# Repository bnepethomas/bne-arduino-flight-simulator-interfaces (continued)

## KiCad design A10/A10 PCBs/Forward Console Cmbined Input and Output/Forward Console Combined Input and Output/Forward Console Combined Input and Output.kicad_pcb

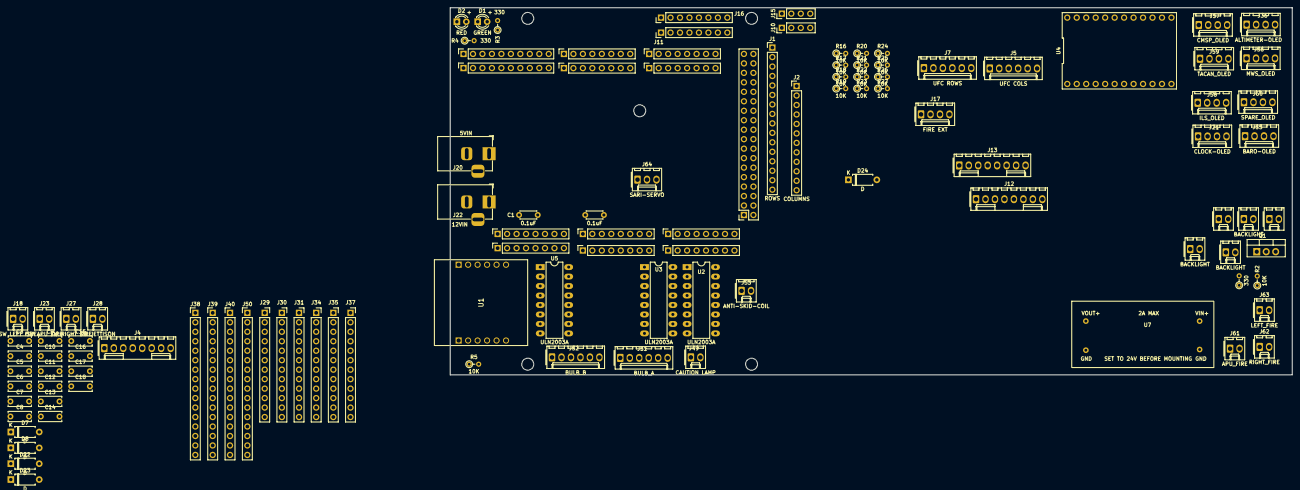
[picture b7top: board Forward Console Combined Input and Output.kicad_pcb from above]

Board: 2 copper layers, 225.7 x 98.4 mm, 116 parts (0 on the bottom side), 201 nets, no tracks yet.

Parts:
C1, C2: 0.1uF; C_Disc_D4.3mm_W1.9mm_P5.00mm
C3, C4, C5, C6, C7, C8, C9, C10, C11, C12, C13, C14, C15, C16, C17, C18: 0.1uF; C_Disc_D6.0mm_W2.5mm_P5.00mm
D1: GREEN; LED_D3.0mm
D2: RED; LED_D3.0mm
D7, D8, D22, D23, D24: D; D_A-405_P7.62mm_Horizontal
H1, H2, H3, H4: MountingHole; MountingHole_3.2mm
J1: ROWS; PinHeader_1x16_P2.54mm_Vertical
J2: COLUMNS; PinHeader_1x12_P2.54mm_Vertical
J3, J6, J9, J14, J19: BACKLIGHT; Molex_KK-254_AE-6410-02A_1x02_P2.54mm_Vertical
J4: MASTER ARM; Molex_KK-254_AE-6410-08A_1x08_P2.54mm_Vertical
J5: UFC COLS; Molex_KK-254_AE-6410-06A_1x06_P2.54mm_Vertical
J7: UFC ROWS; Molex_KK-254_AE-6410-06A_1x06_P2.54mm_Vertical
J10, J15: PATCH; PinHeader_1x04_P2.54mm_Vertical
J11, J16: PATCH; PinHeader_1x08_P2.54mm_Vertical
J12: LANDING GEAR; Molex_KK-254_AE-6410-08A_1x08_P2.54mm_Vertical
J13: NMSP CMSP; Molex_KK-254_AE-6410-08A_1x08_P2.54mm_Vertical
J17: FIRE EXT; Molex_KK-254_AE-6410-04A_1x04_P2.54mm_Vertical
J18: SW LEFT FIRE; Molex_KK-254_AE-6410-02A_1x02_P2.54mm_Vertical
J20: 5VIN; BarrelJack_Horizontal
J21: CLOCK-OLED; Molex_KK-254_AE-6410-04A_1x04_P2.54mm_Vertical
J22: 12VIN; BarrelJack_Horizontal
J23: SW APU FIRE; Molex_KK-254_AE-6410-02A_1x02_P2.54mm_Vertical
J24, J46: PWM; PinSocket_1x10_P2.54mm_Vertical
J25, J47: PWM; PinSocket_1x08_P2.54mm_Vertical
J26, J48: Communication; PinSocket_1x08_P2.54mm_Vertical
J27: SW RIGHT FIRE; Molex_KK-254_AE-6410-02A_1x02_P2.54mm_Vertical
J28: SW JETTISON; Molex_KK-254_AE-6410-02A_1x02_P2.54mm_Vertical
J29, J30, J31, J34, J35, J37: PATCH; PinSocket_1x12_P2.54mm_Vertical
J32, J33, J43, J44: Analog; PinSocket_1x08_P2.54mm_Vertical
J36: ALTIMETER-OLED; Molex_KK-254_AE-6410-04A_1x04_P2.54mm_Vertical
J38, J39, J40, J50: PATCH; PinHeader_1x16_P2.54mm_Vertical
J41, J42: Power; PinSocket_1x08_P2.54mm_Vertical
J45: Digital; PinSocket_2x18_P2.54mm_Vertical
J49: CAUTION LAMP; Molex_KK-254_AE-6410-02A_1x02_P2.54mm_Vertical
J51: BULB_A; Molex_KK-254_AE-6410-06A_1x06_P2.54mm_Vertical
J52: BULB_B; Molex_KK-254_AE-6410-06A_1x06_P2.54mm_Vertical
J53: ANTI-SKID-COIL; Molex_KK-254_AE-6410-02A_1x02_P2.54mm_Vertical
J55: BARO-OLED; Molex_KK-254_AE-6410-04A_1x04_P2.54mm_Vertical
J56: MWS_OLED; Molex_KK-254_AE-6410-04A_1x04_P2.54mm_Vertical
J57: CMSP_OLED; Molex_KK-254_AE-6410-04A_1x04_P2.54mm_Vertical
J58: ILS_OLED; Molex_KK-254_AE-6410-04A_1x04_P2.54mm_Vertical
J59: TACAN_OLED; Molex_KK-254_AE-6410-04A_1x04_P2.54mm_Vertical
J60: SPARE_OLED; Molex_KK-254_AE-6410-04A_1x04_P2.54mm_Vertical
J61: APU_FIRE; Molex_KK-254_AE-6410-02A_1x02_P2.54mm_Vertical
J62: RIGHT_FIRE; Molex_KK-254_AE-6410-02A_1x02_P2.54mm_Vertical
J63: LEFT_FIRE; Molex_KK-254_AE-6410-02A_1x02_P2.54mm_Vertical
J64: SARI-SERVO; Molex_KK-254_AE-6410-03A_1x03_P2.54mm_Vertical
MH1: MountingHole_3.2mm
Q1: IRF1405PBF; TO-220-3_Vertical
R1, R3, R4: 330; R_Axial_DIN0204_L3.6mm_D1.6mm_P2.54mm_Vertical
R2, R5, R16, R17, R18, R19, R20, R21, R22, R23, R24, R25, R26, R27: 10K; R_Axial_DIN0204_L3.6mm_D1.6mm_P2.54mm_Vertical
U1: USR-ES1; USRES1
U2, U3, U5: ULN2003A; DIP-16_W7.62mm_LongPads
U4: TCA9548APWR; DIP-24_TCA9548A
U7: VIRIABLE BUCK; VARIABLE_BUCK

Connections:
+3V3: J41.4, J42.4, R5.1, U1.B2 (3V3_1), U1.B3 (3V3_2), U4.1 (VCC)
+5V: J21.1, J36.1, J41.5, J42.5, J45.35, J45.36, J55.1, J56.1, J57.1, J58.1, J59.1, J60.1, R16.1, R17.1, R18.1, R19.1, R20.1, R21.1, R22.1, R23.1, R24.1, R25.1, R26.1, R27.1
+5VD: C1.1, J20.1, J64.1
+12V: C2.1, J3.1, J6.1, J9.1, J14.1, J19.1, J22.1, J49.1, J51.1, J52.1, J53.1, U2.9 (COM), U3.9 (COM), U7.1 (VIN)
+24V: J61.1, J62.1, J63.1, U5.9 (COM), U7.4 (24V_OUT)
/*12: J24.6, J46.6, R4.1
/*13: J24.5, J46.5, R3.1
/AREF: J24.3, J46.3
/COIL AND LAMP DRIVERS/ANCHR: J52.4, U3.15 (O2)
/COIL AND LAMP DRIVERS/B_APU_FIRE: J61.2, U5.15 (O2)
/COIL AND LAMP DRIVERS/B_LEFT_FIRE: J63.2, U5.16 (O1)
/COIL AND LAMP DRIVERS/B_RIGHT_FIRE: J62.2, U5.14 (O3)
/COIL AND LAMP DRIVERS/CAUTION_LAMP-: J49.2, U2.16 (O1)
/COIL AND LAMP DRIVERS/COIL_ANTI_SKID: J53.2, U3.12 (O5)
/COIL AND LAMP DRIVERS/EGI: J51.6, U2.11 (O6)
/COIL AND LAMP DRIVERS/HARS: J51.5, U2.12 (O5)
/COIL AND LAMP DRIVERS/ILS: J52.6, U3.13 (O4)
/COIL AND LAMP DRIVERS/MISSLE LAUNCH: J51.4, U2.13 (O4)
/COIL AND LAMP DRIVERS/PRI: J51.2, U2.15 (O2)
/COIL AND LAMP DRIVERS/SEP: J51.3, U2.14 (O3)
/COIL AND LAMP DRIVERS/STR PT: J52.3, U3.16 (O1)
/COIL AND LAMP DRIVERS/TCN: J52.5, U3.14 (O3)
/COIL AND LAMP DRIVERS/TISL: J52.2, U2.10 (O7)
/IOREF: J41.2, J42.2
/OLED/SC0: J21.3, U4.10 (SC0)
/OLED/SC1: J36.3, U4.12 (SC1)
/OLED/SC2: J55.3, U4.14 (SC2)
/OLED/SC3: J56.3, U4.16 (SC3)
/OLED/SC4: J57.3, U4.18 (SC4)
/OLED/SC5: J58.3, U4.20 (SC5)
/OLED/SC6: J59.3, U4.22 (SC6)
/OLED/SC7: J60.3, U4.24 (SC7)
/OLED/SD0: J21.4, U4.9 (SD0)
/OLED/SD1: J36.4, U4.11 (SD1)
/OLED/SD2: J55.4, U4.13 (SD2)
/OLED/SD3: J56.4, U4.15 (SD3)
/OLED/SD4: J57.4, U4.17 (SD4)
/OLED/SD5: J58.4, U4.19 (SD5)
/OLED/SD6: J59.4, U4.21 (SD6)
/OLED/SD7: J60.4, U4.23 (SD7)
/RX0/0: J25.8, J47.8
/TX0/1: J25.7, J47.7
/~RESET: J41.3, J42.3
A0 D54: C18.1, J32.1, J43.1, U5.1 (I1)
A1 D55: C16.1, J32.2, J43.2, U5.2 (I2)
A2 D56: C14.1, J32.3, J43.3, U5.3 (I3)
A3 D57: C12.1, J32.4, J43.4
A4 D58: C10.1, J32.5, J43.5, U2.1 (I1)
A5 D59: C8.1, J32.6, J43.6, U2.2 (I2)
A6 D60: C5.1, J32.7, J43.7, U2.3 (I3)
A7 D61: C3.1, J32.8, J43.8, U2.4 (I4)
A8 D62: C17.1, J33.1, J44.1, U2.5 (I5)
A9 D63: C15.1, J33.2, J44.2, U2.6 (I6)
A10 D64: C13.1, J33.3, J44.3, U2.7 (I7)
A11 D65: C11.1, J33.4, J44.4, U3.1 (I1)
A12 D66: C9.1, J33.5, J44.5, U3.2 (I2)
A13 D67: C7.1, J33.6, J44.6, U3.3 (I3)
A14 D68: C6.1, J33.7, J44.7, U3.4 (I4)
A15 D69: C4.1, J33.8, J44.8, U3.5 (I5)
BACKLIGHT: J25.6, J47.6, R1.2
BACKLIGHT_-V: J3.2, J6.2, J9.2, J14.2, J19.2, Q1.2 (D)
D3: J25.5, J47.5
D4: J25.4, J47.4
D5: J25.3, J47.3
D6: J25.2, J47.2
D7: J25.1, J47.1
D8: J24.10, J46.10
D9: J24.9, J46.9
D11: J24.7, J46.7
D14: J26.1, J48.1, J64.2
D15: J26.2, J48.2
D16: J26.3, J48.3, U4.5 (~RESET)
D17: J26.4, J48.4, U4.8 (A2)
D18: J26.5, J48.5, U4.7 (A1)
D19: J26.6, J48.6, U4.6 (A0)
D20 SDA: J24.2, J26.7, J46.2, J48.7, U4.3 (SDA)
D21 SCL: J24.1, J26.8, J46.1, J48.8, U4.4 (SCL)
D22: J1.1, J7.1, J45.33
D23: J1.2, J7.2, J45.34
D24: J1.3, J7.3, J45.31
D25: J1.4, J7.4, J45.32
D26: J1.5, J7.5, J45.29
D27: J1.6, J7.6, J45.30
D28: J1.7, J4.5, J13.3, J45.27
D29: J1.8, J4.6, J13.4, J45.28
D30: J1.9, J4.7, J13.5, J45.25
D31: J1.10, J4.8, J13.6, J45.26
D32: J1.11, J12.3, J13.7, J17.2, J18.2, J45.23
D33: J1.12, J12.4, J13.8, J17.4, J23.2, J45.24
D34: J1.13, J12.5, J27.2, J45.21
D35: J1.14, J12.6, J28.2, J45.22
D36: J1.15, J12.7, J45.19
D37: J1.16, J12.8, J45.20
D38: J2.1, J4.1, J5.1, J12.1, J45.17, R16.2
D39: J2.2, J4.2, J5.2, J12.2, J45.18, R17.2
D40: D8.2 (A), D22.2 (A), D23.2 (A), D24.2 (A), J2.3, J4.3, J5.3, J45.15, R18.2
D41: D7.2 (A), J2.4, J4.4, J5.4, J45.16, R19.2
D42: J2.5, J5.5, J13.1, J45.13, R20.2
D43: J2.6, J5.6, J13.2, J45.14, R21.2
D44: J2.7, J45.11, R22.2
D45: J2.8, J45.12, R23.2
D46: J2.9, J45.9, R24.2
D47: J2.10, J45.10, R25.2
D48: J2.11, J45.7, R26.2
D49: J2.12, J45.8, R27.2
ES1_RST: J45.4, U1.B5 (RST)
GND: C1.2, C2.2, C3.2, C4.2, C5.2, C6.2, C7.2, C8.2, C9.2, C10.2, C11.2, C12.2, C13.2, C14.2, C15.2, C16.2, C17.2, C18.2, D1.1 (K), D2.1 (K), J20.2, J21.2, J22.2, J24.4, J36.2, J41.6, J41.7, J42.6, J42.7, J45.1, J45.2, J46.4, J55.2, J56.2, J57.2, J58.2, J59.2, J60.2, J64.3, Q1.3 (S), R2.1, U1.A1 (GND_1), U1.A2 (GND_2), U1.B1 (GND_3), U2.8 (GND), U3.6 (I6), U3.7 (I7), U3.8 (GND), U4.2 (GND), U5.6 (I6), U5.7 (I7), U5.8 (GND), U7.2 (GND), U7.3 (GND)
MISO: J45.5, U1.B6 (MISO)
MOSI: J45.6, U1.A3 (MOSI)
unnamed: D1.2 (A), R3.2
unnamed: D2.2 (A), R4.2
unnamed: D7.1 (K), J17.1, J17.3
unnamed: D8.1 (K), J18.1
unnamed: D22.1 (K), J23.1
unnamed: D23.1 (K), J27.1
unnamed: D24.1 (K), J28.1
unnamed: J10.1, J15.1
unnamed: J10.2, J15.2
unnamed: J10.3, J15.3
unnamed: J10.4, J15.4
unnamed: J11.1, J16.1
unnamed: J11.2, J16.2
unnamed: J11.3, J16.3
unnamed: J11.4, J16.4
unnamed: J11.5, J16.5
unnamed: J11.6, J16.6
unnamed: J11.7, J16.7
unnamed: J11.8, J16.8
unnamed: J29.1, J30.1
unnamed: J29.2, J30.2
unnamed: J29.3, J30.3
unnamed: J29.4, J30.4
unnamed: J29.5, J30.5
unnamed: J29.6, J30.6
unnamed: J29.7, J30.7
unnamed: J29.8, J30.8
unnamed: J29.9, J30.9
unnamed: J29.10, J30.10
unnamed: J29.11, J30.11
unnamed: J29.12, J30.12
unnamed: J31.1, J34.1
unnamed: J31.2, J34.2
unnamed: J31.3, J34.3
unnamed: J31.4, J34.4
unnamed: J31.5, J34.5
unnamed: J31.6, J34.6
unnamed: J31.7, J34.7
unnamed: J31.8, J34.8
unnamed: J31.9, J34.9
unnamed: J31.10, J34.10
unnamed: J31.11, J34.11
unnamed: J31.12, J34.12
unnamed: J35.1, J37.1
unnamed: J35.2, J37.2
unnamed: J35.3, J37.3
unnamed: J35.4, J37.4
unnamed: J35.5, J37.5
unnamed: J35.6, J37.6
unnamed: J35.7, J37.7
unnamed: J35.8, J37.8
unnamed: J35.9, J37.9
unnamed: J35.10, J37.10
unnamed: J35.11, J37.11
unnamed: J35.12, J37.12
unnamed: J38.1, J39.1
unnamed: J38.2, J39.2
unnamed: J38.3, J39.3
unnamed: J38.4, J39.4
unnamed: J38.5, J39.5
unnamed: J38.6, J39.6
unnamed: J38.7, J39.7
unnamed: J38.8, J39.8
unnamed: J38.9, J39.9
unnamed: J38.10, J39.10
unnamed: J38.11, J39.11
unnamed: J38.12, J39.12
unnamed: J38.13, J39.13
unnamed: J38.14, J39.14
unnamed: J38.15, J39.15
unnamed: J38.16, J39.16
unnamed: J40.1, J50.1
unnamed: J40.2, J50.2
unnamed: J40.3, J50.3
unnamed: J40.4, J50.4
unnamed: J40.5, J50.5
unnamed: J40.6, J50.6
unnamed: J40.7, J50.7
unnamed: J40.8, J50.8
unnamed: J40.9, J50.9
unnamed: J40.10, J50.10
unnamed: J40.11, J50.11
unnamed: J40.12, J50.12
unnamed: J40.13, J50.13
unnamed: J40.14, J50.14
unnamed: J40.15, J50.15
unnamed: J40.16, J50.16
unnamed: Q1.1 (G), R1.1, R2.2
unnamed: R5.2, U1.A6 (INT)
SCLK: J45.3, U1.A4 (SCLK)
SS: J24.8, J46.8, U1.A5 (CS)
VCC: J41.8, J42.8
